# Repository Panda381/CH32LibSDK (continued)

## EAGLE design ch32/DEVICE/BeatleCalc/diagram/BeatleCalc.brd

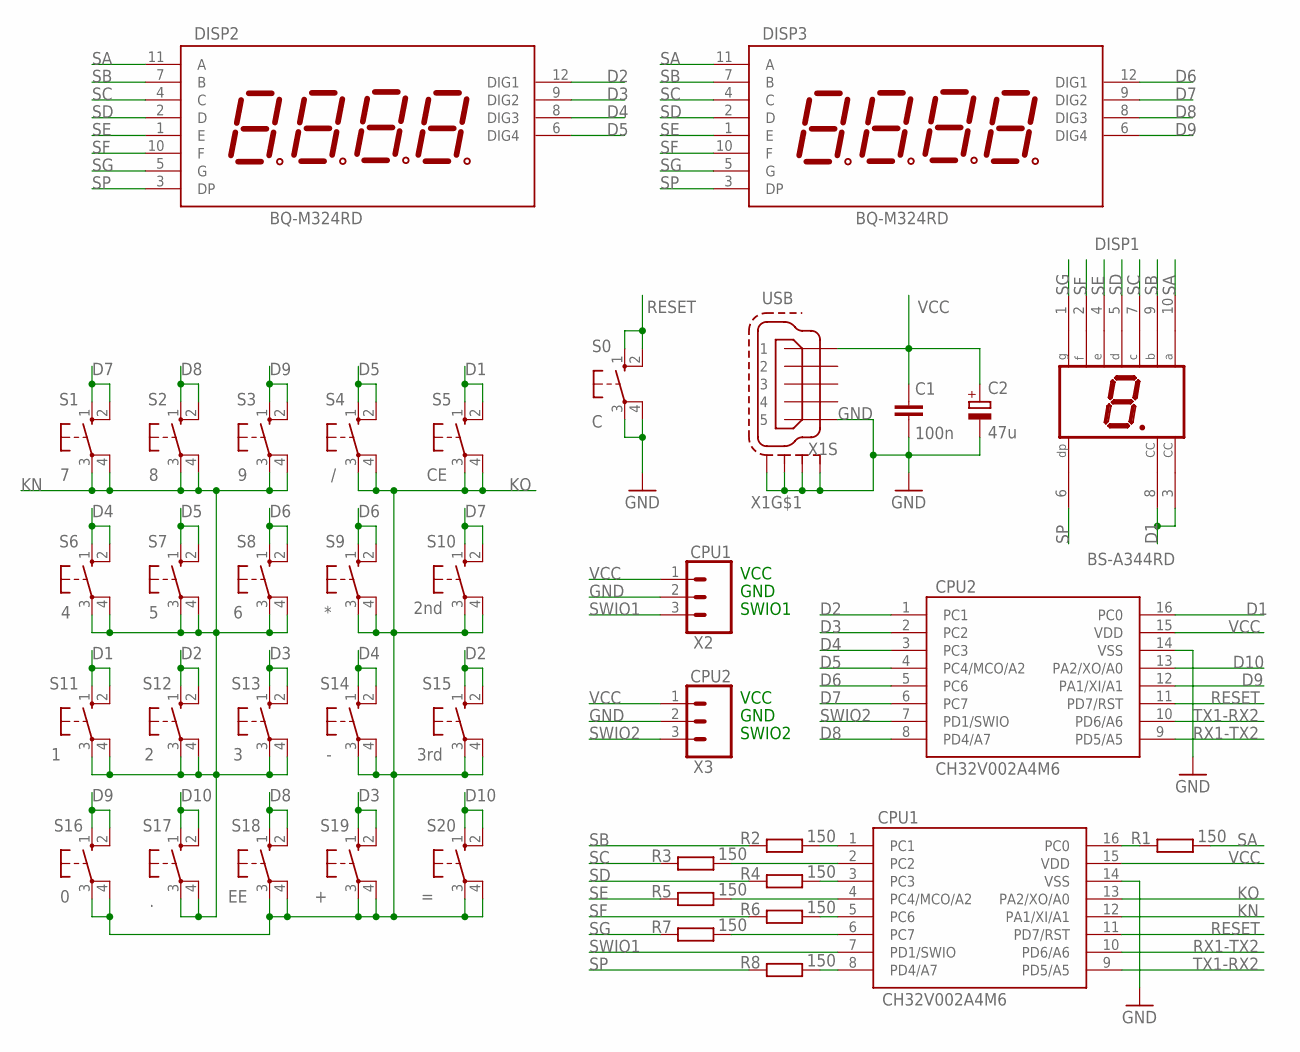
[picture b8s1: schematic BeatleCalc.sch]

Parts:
C1: 100n; C050-024X044
C2: 47u; TT2D6L
CPU1, CPU2: CH32V002A4M6; SOP16
DISP1: BS-A344RD; HDSP-E
DISP2, DISP3: BQ-M324RD; 4DIG_7SEG_92MM
R1, R2, R3, R4, R5, R6, R7, R8: 150; 0204/10
S0: C; B3F-10XX
S1: 7; B3F-10XX
S2: 8; B3F-10XX
S3: 9; B3F-10XX
S4: /; B3F-10XX
S5: CE; B3F-10XX
S6: 4; B3F-10XX
S7: 5; B3F-10XX
S8: 6; B3F-10XX
S9: *; B3F-10XX
S10: 2nd; B3F-10XX
S11: 1; B3F-10XX
S12: 2; B3F-10XX
S13: 3; B3F-10XX
S14: -; B3F-10XX
S15: 3rd; B3F-10XX
S16: 0; B3F-10XX
S17: .; B3F-10XX
S18: EE; B3F-10XX
S19: +; B3F-10XX
S20: =; B3F-10XX
X1: USB; 32005-201
X2: CPU1; 1X03_LONGPADS
X3: CPU2; 1X03_LONGPADS

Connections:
D1: CPU2.16 (PC0), DISP1.3 (CC), DISP1.8 (CC), S5.1 (S), S5.2 (S1), S11.1 (S), S11.2 (S1)
D2: CPU2.1 (PC1), DISP2.12 (DIG1), S12.1 (S), S12.2 (S1), S15.1 (S), S15.2 (S1)
D3: CPU2.2 (PC2), DISP2.9 (DIG2), S13.1 (S), S13.2 (S1), S19.1 (S), S19.2 (S1)
D4: CPU2.3 (PC3), DISP2.8 (DIG3), S6.1 (S), S6.2 (S1), S14.1 (S), S14.2 (S1)
D5: CPU2.4 (PC4/MCO/A2), DISP2.6 (DIG4), S4.1 (S), S4.2 (S1), S7.1 (S), S7.2 (S1)
D6: CPU2.5 (PC6), DISP3.12 (DIG1), S8.1 (S), S8.2 (S1), S9.1 (S), S9.2 (S1)
D7: CPU2.6 (PC7), DISP3.9 (DIG2), S1.1 (S), S1.2 (S1), S10.1 (S), S10.2 (S1)
D8: CPU2.8 (PD4/A7), DISP3.8 (DIG3), S2.1 (S), S2.2 (S1), S18.1 (S), S18.2 (S1)
D9: CPU2.12 (PA1/XI/A1), DISP3.6 (DIG4), S3.1 (S), S3.2 (S1), S16.1 (S), S16.2 (S1)
D10: CPU2.13 (PA2/XO/A0), S17.1 (S), S17.2 (S1), S20.1 (S), S20.2 (S1)
GND: C1.2, C2.-, CPU1.14 (VSS), CPU2.14 (VSS), S0.3, S0.4 (P1), X1.5, X1.M1 (S1), X1.M2 (S2), X1.M3 (S3), X1.M4 (S4), X2.2, X3.2
KN: CPU1.12 (PA1/XI/A1), S1.3, S1.4 (P1), S2.3, S2.4 (P1), S3.3, S3.4 (P1), S6.3, S6.4 (P1), S7.3, S7.4 (P1), S8.3, S8.4 (P1), S11.3, S11.4 (P1), S12.3, S12.4 (P1), S13.3, S13.4 (P1), S17.3, S17.4 (P1)
KO: CPU1.13 (PA2/XO/A0), S4.3, S4.4 (P1), S5.3, S5.4 (P1), S9.3, S9.4 (P1), S10.3, S10.4 (P1), S14.3, S14.4 (P1), S15.3, S15.4 (P1), S16.3, S16.4 (P1), S18.3, S18.4 (P1), S19.3, S19.4 (P1), S20.3, S20.4 (P1)
unnamed: CPU1.1 (PC1), R2.2
unnamed: CPU1.2 (PC2), R3.2
unnamed: CPU1.3 (PC3), R4.2
unnamed: CPU1.4 (PC4/MCO/A2), R5.2
unnamed: CPU1.5 (PC6), R6.2
unnamed: CPU1.6 (PC7), R7.2
unnamed: CPU1.8 (PD4/A7), R8.2
unnamed: CPU1.16 (PC0), R1.1
RESET: CPU1.11 (PD7/RST), CPU2.11 (PD7/RST), S0.1 (S), S0.2 (S1)
RX1-TX2: CPU1.10 (PD6/A6), CPU2.9 (PD5/A5)
SA: DISP1.10 (A), DISP2.11 (A), DISP3.11 (A), R1.2
SB: DISP1.9 (B), DISP2.7 (B), DISP3.7 (B), R2.1
SC: DISP1.7 (C), DISP2.4 (C), DISP3.4 (C), R3.1
SD: DISP1.5 (D), DISP2.2 (D), DISP3.2 (D), R4.1
SE: DISP1.4 (E), DISP2.1 (E), DISP3.1 (E), R5.1
SF: DISP1.2 (F), DISP2.10 (F), DISP3.10 (F), R6.1
SG: DISP1.1 (G), DISP2.5 (G), DISP3.5 (G), R7.1
SP: DISP1.6 (DP), DISP2.3 (DP), DISP3.3 (DP), R8.1
SWIO1: CPU1.7 (PD1/SWIO), X2.3
SWIO2: CPU2.7 (PD1/SWIO), X3.3
TX1-RX2: CPU1.9 (PD5/A5), CPU2.10 (PD6/A6)
VCC: C1.1, C2.+, CPU1.15 (VDD), CPU2.15 (VDD), X1.1, X2.1, X3.1

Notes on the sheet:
VCC
GND
SWIO2
SWIO1

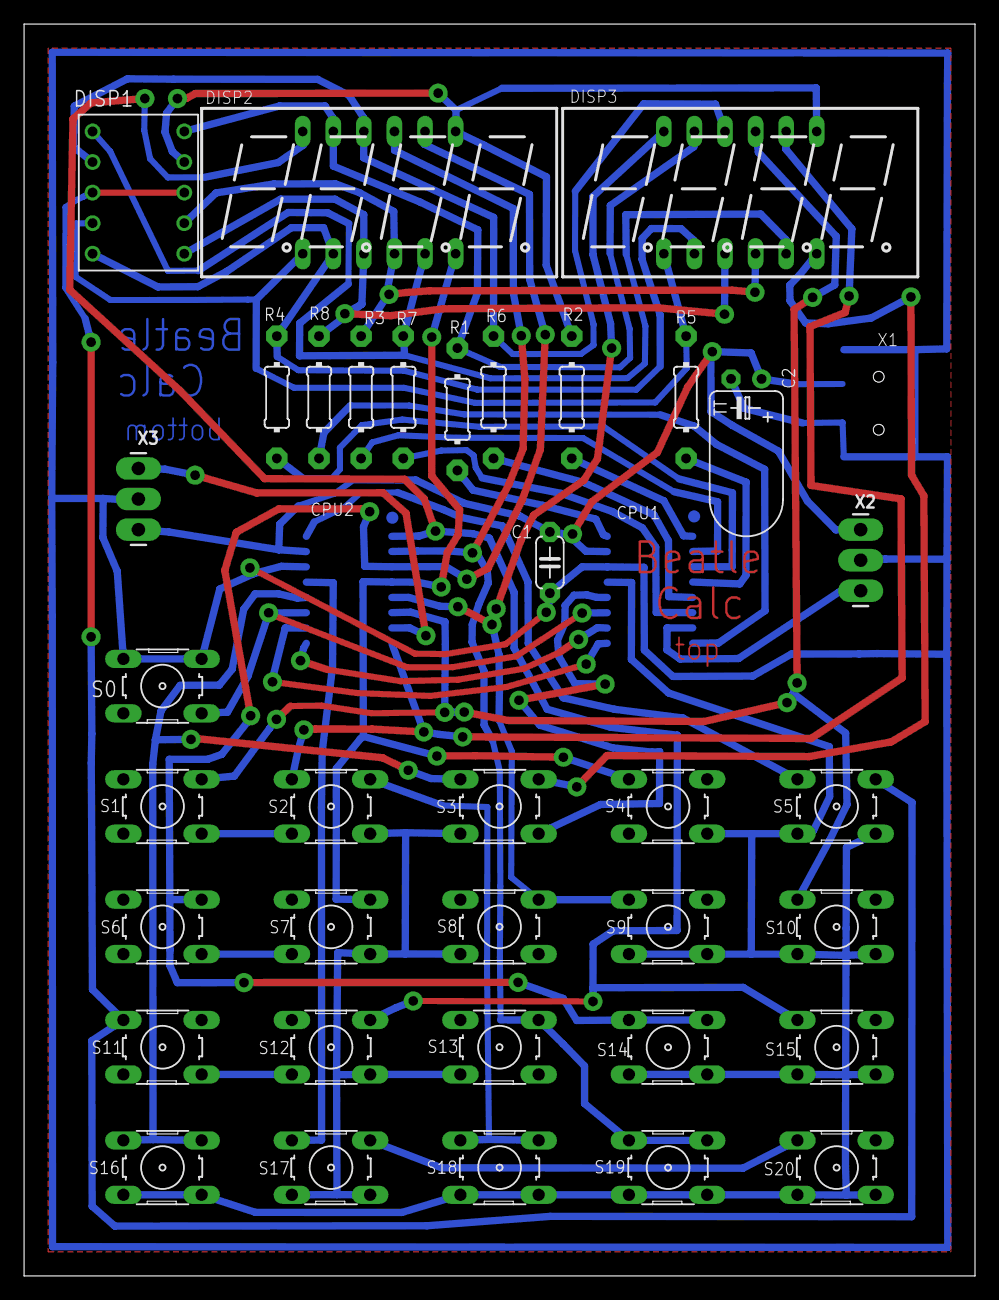
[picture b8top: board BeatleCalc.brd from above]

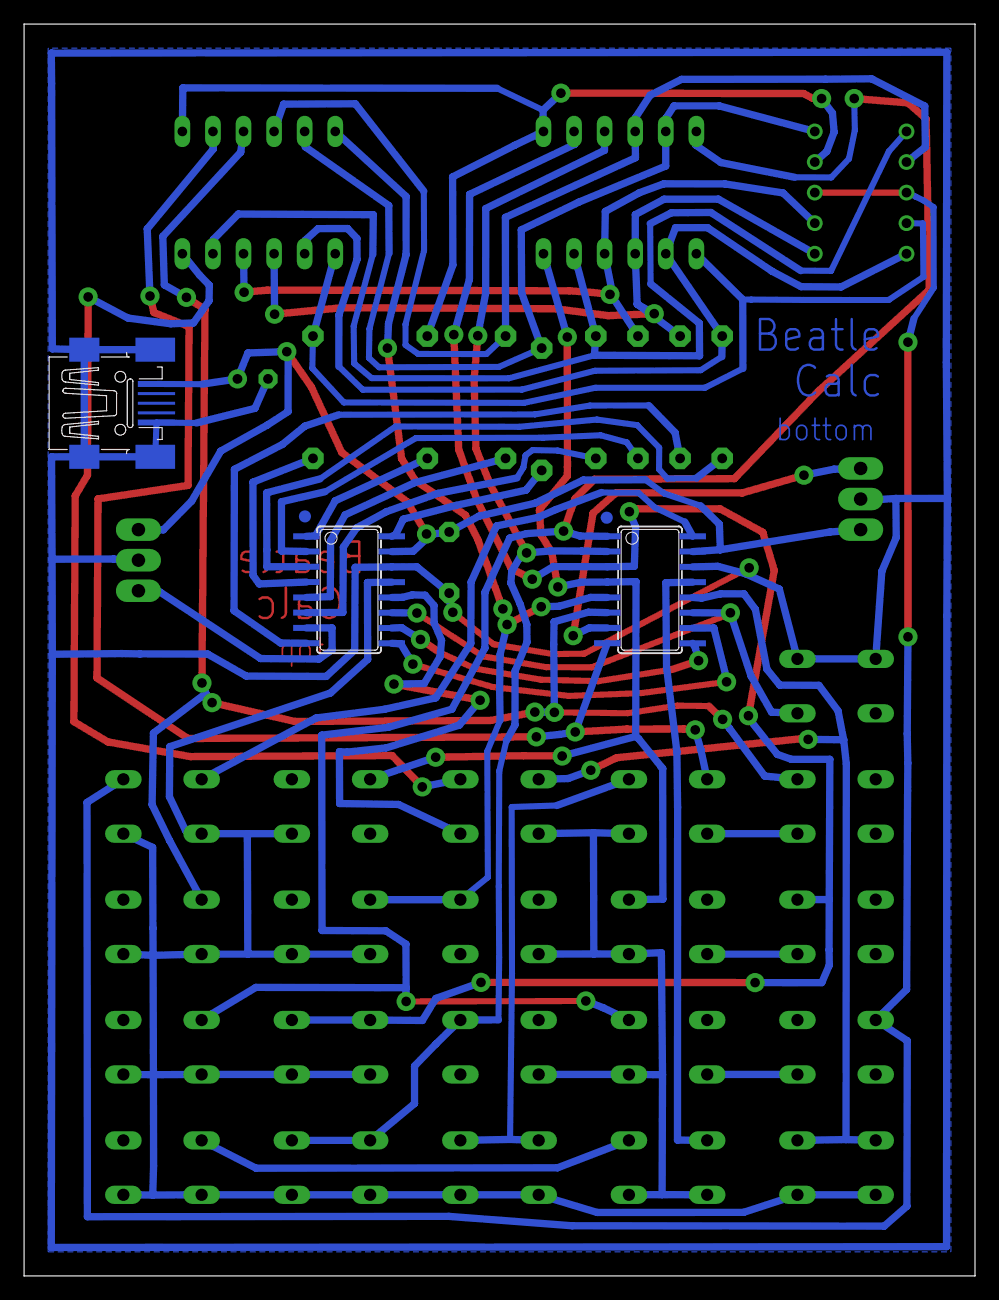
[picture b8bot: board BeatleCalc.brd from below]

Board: 2 copper layers, 79.0 x 104.0 mm, 39 parts (3 on the bottom side), 35 nets.

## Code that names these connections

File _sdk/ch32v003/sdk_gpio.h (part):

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INLINE void GPIOA_Out1(int pin) { GPIOx_Out1(GPIOA, pin); }
INLINE void GPIOC_Out1(int pin) { GPIOx_Out1(GPIOC, pin); }
INLINE void GPIOD_Out1(int pin) { GPIOx_Out1(GPIOD, pin); }
INLINE void GPIO_Out1(int gpio) { GPIOx_Out1(GPIO_PORT(gpio), GPIO_PIN(gpio)); }

// output value to GPIO output pin (val = 0 or <>0; port = GPIOA..., pin = 0.., gpio = PA0...)
//  In GPIO_MODE_IN_* modes 0 selects pull-down mode, <>0 selects pull-up mode.
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INLINE void GPIO_Remap1_3b(int pos, int map) { AFIO->PCFR1 = (AFIO->PCFR1 & ~(7 << pos)) | (map << pos); }

// Remap SPI1 (default 0)
//	0 ... PC1:CS, PC5:SCK, PC7:MISO, PC6:MOSI
//	1 ... PC0:CS, PC5:SCK, PC7:MISO, PC6:MOSI
INLINE void GPIO_Remap_SPI1(int map) { GPIO_Remap1_1b(0, map); }

// Remap I2C1 (default 0)
//	0 ... PC2:SCL, PC1:SDA
//	1 ... PD1:SCL, PD0:SDA
//	2,3 ... PC5:SCL, PC6:SDA
INLINE void GPIO_Remap_I2C1(int map) { AFIO->PCFR1 = (AFIO->PCFR1 & ~(B1|B22)) | ((map & B0) << 1) | ((map >> 1) << 22); }

// Remap USART1 (default 0)
//	0 ... PD5:TX, PD6:RX, PD4:CLK, PD3:CTS, PC2:RTS
//	1 ... PD0:TX, PD1:RX, PD7:CLK, PC3:CTS, PC2:RTS, PD0:SW_RX
//	2 ... PD6:TX, PD5:RX, PD7:CLK, PC6:CTS, PC7:RTS, PD6:SW_RX
//	3 ... PC0:TX, PC1:RX, PC5:CLK, PC6:CTS, PC7:RTS, PC0:SW_RX
INLINE void GPIO_Remap_USART1(int map) { AFIO->PCFR1 = (AFIO->PCFR1 & ~(B2|B21)) | ((map & B0) << 2) | ((map >> 1) << 21); }

// Remap Timer 1 (default 0)
//	0 ... PC5:ETR, PD2:CH1, PA1:CH2, PC3:CH3, PC4:CH4, PC2:BKIN, PD0:CH1N, PA2:CH2N, PD1:CH3N
//	1 ... PC5:ETR, PC6:CH1, PC7:CH2, PC0:CH3, PD3:CH4, PC1:BKIN, PC3:CH1N, PC4:CH2N, PD1:CH3N
//	2 ... PD4:ETR, PD2:CH1, PA1:CH2, PC3:CH3, PC4:CH4, PC2:BKIN, PD0:CH1N, PA2:CH2N, PD1:CH3N
//	3 ... PC2:ETR, PC4:CH1, PC7:CH2, PC5:CH3, PD4:CH4, PC1:BKIN, PC3:CH1N, PD2:CH2N, PC6:CH3N
INLINE void GPIO_Remap_TIM1(int map) { GPIO_Remap1_2b(6, map); }

// Remap Timer 2 (default 0)
//	0 ... PD4:CH1/ETR, PD3:CH2, PC0:CH3, PD7:CH4
//	1 ... PC5:CH1/ETR, PC2:CH2, PD2:CH3, PC1:CH4
//	2 ... PC1:CH1/ETR, PD3:CH2, PC0:CH3, PD7:CH4
//	3 ... PC1:CH1/ETR, PC7:CH2, PD6:CH3, PD5:CH4
INLINE void GPIO_Remap_TIM2(int map) { GPIO_Remap1_2b(8, map); }

// Remap PA1 & PA2 pins to OSC_IN & OSC_OUT (default 0)
//	0 ... pins PA1 & PA2 are used as GPIO ports
//	1 ... pins PA1 & PA2 are used as crystal pins OSC_IN & OSC_OUT
INLINE void GPIO_Remap_PA1PA2(int map) { GPIO_Remap1_1b(15, map); }

// Remap ADC1 external trigger injection conversion (default 0)
//	0 ... ADC1 external trigger injection conversion connected to PD3
//	1 ... ADC1 external trigger injection conversion connected to PC2
INLINE void GPIO_Remap_ADC1INJ(int map) { GPIO_Remap1_1b(17, map); }

// Remap ADC1 external trigger regular conversion (default 0)
//	0 ... ADC1 external trigger regular conversion connected to PD3
//	1 ... ADC1 external trigger regular conversion connected to PC2
INLINE void GPIO_Remap_ADC1REG(int map) { GPIO_Remap1_1b(18, map); }

// Remap Timer 1 Channel 1 (default 0)
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
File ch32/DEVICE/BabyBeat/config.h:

// ****************************************************************************
//                                 
//                        Project library configuration
//
// ****************************************************************************

#ifndef _CONFIG_H
#define _CONFIG_H

// Pre-set defines (use #if to check):
//	target MCU	MCU serie	MCU class	MCU subclass
//	CH32V002x4	CH32V002	CH32V0		CH32V00X
//	CH32V003x4	CH32V003	CH32V0
//	CH32V004x6	CH32V004	CH32V0		CH32V00X
//	CH32V005x6	CH32V005	CH32V0		CH32V00X
//	CH32V006x4	CH32V006	CH32V0		CH32V00X
//	CH32V006x8	CH32V006	CH32V0		CH32V00X
//	CH32V007x8	CH32V007	CH32V0		CH32V00X
//	CH32X033x8	CH32V033	CH32V0		CH32V03X
//	CH32X035x7	CH32V035	CH32V0		CH32V03X
//	CH32X035x8	CH32V035	CH32V0		CH32V03X
//	CH32V103x6	CH32V103	CH32V1
//	CH32V103x8	CH32V103	CH32V1
//	CH32L103x8	CH32L103	CH32V1

// FLASHSIZE ... Flash size in bytes
// RAMSIZE ... RAM size in bytes
// STACKSIZE ... Stack size in bytes

#define BABYBEAT	1	// 1 = use BabyBeat device
//#define BEATLEBEAT	1	// 1 = use BeatleBeat device

#if BABYBEAT		// 1 = use BabyBeat device
#define SYSTICK_KEYSCAN	1	// 1=call KeyScan() function from SysTick system timer
#else
#define SYSTICK_KEYSCAN	0	// 1=call KeyScan() function from SysTick system timer
#endif

// ----------------------------------------------------------------------------
//                            Clock Setup
// ----------------------------------------------------------------------------

// frequency of HSI internal oscillator 48MHz
#define HSI_VALUE	24000000

// System clock source: 1=HSI, 2=HSE, 3=HSE_Bypass, 4=PLL_HSI, 5=PLL_HSE, 6=PLL_HSE_Bypass, 7=PLL_HSI/2, 8=PLL_HSE/2, 9=PLL_HSE_Bypass/2
#define SYSCLK_SRC	4

// PLL multiplier
#define PLLCLK_MUL	2		// only *2 supported; 24 MHz * 2 = 48 MHz

// System clock divider: 1, 2, 3, 4, 5, 6, 7, 8, 16, 32, 64, 128, 256 (default 1)
#define SYSCLK_DIV	1

// ADC clock divider: (1,) 2, 4, 6, 8, 12, 16, 24, 32, 48, 64, 96, 128 (default 1 or 2)
#define ADCCLK_DIV	8		// CH32V0: max. 24 MHz (48 / 8 = 6 MHz)

// number of HCLK clock cycles per 1 us (used with Wait functions)
// - If you want to change frequency of system clock run-time, use a variable instead of constant.
#define HCLK_PER_US	48

// increment of system time in [ms] on SysTick interrupt (0=do not use SysTick interrupt)
#if BABYBEAT		// 1 = use BabyBeat device
#define SYSTICK_MS	20
#else
#define SYSTICK_MS	0
#endif

// ----------------------------------------------------------------------------
//                          Peripheral clock enable
// ----------------------------------------------------------------------------

#define ENABLE_SRAM	1		// SRAM enable
#define ENABLE_FLASH	0		// FLASH enable
#define ENABLE_WWDG	0		// Window watchdog enable
#define ENABLE_PWR	1		// Power module enable
#define ENABLE_AFI	1		// I/O auxiliary function enable
#define ENABLE_PA	1		// PA port enable
#define ENABLE_PB	0		// PB port enable
#define ENABLE_PC	1		// PC port enable
#define ENABLE_PD	1		// PD port enable
#define ENABLE_ADC1	0		// ADC1 module enable
#define ENABLE_TIM1	1		// TIM1 module enable
#define ENABLE_TIM2	0		// TIM2 module enable
#define ENABLE_TIM3	0		// TIM3 module enable
#define ENABLE_SPI1	0		// SPI1 module enable
#define ENABLE_USART1	0		// USART1 module enable
#define ENABLE_I2C1	0		// I2C1 module enable
#define ENABLE_DMA1	0		// DMA1 module enable

// ----------------------------------------------------------------------------
//                            Library modules
// ----------------------------------------------------------------------------

#define USE_CRC		0	// 1=use CRC library
#define USE_DECNUM	0	// 1=use decode number
#define USE_FAT		1	// 1=use FAT filesystem
#define USE_RAND	0	// 1=use random number generator

// SD card
#if BABYBEAT		// 1 = use BabyBeat device
// Note: cannot use hardware SPI at this CPU, mappings 3 and 4 are not working.
#define SD_CS_GPIO	PA1	// CS output to SD card
#define SD_CLK_GPIO	PD4	// CLK output to SD card
#define SD_MISO_GPIO	PD5	// MISO input from SD card
#define SD_MOSI_GPIO	PD6	// MOSI output to SD card
#else // BABYBEAT
// SD card
#define SD_CS_GPIO	PC4	// CS output to SD card
#define SD_CLK_GPIO	PC2	// CLK output to SD card
#define SD_MISO_GPIO	PC1	// MISO input from SD card
#define SD_MOSI_GPIO	PD1	// MOSI output to SD card
#endif // BABYBEAT
#define USE_SD		3	// use SD card driver: 0=no, 1=software, 2=hardware (with software CS), 3=software with fast read
#define SD_SPEED_INIT	(HCLK_PER_US*2)	// SD speed on init: wait delay "HCLK_PER_US*2" = 250 kbps
#define SD_SPEED_READ	3	// (working value 0..3) SD speed on read: wait delay "HCLK_PER_US/8" = 4 Mbps
#define SD_SPEED_WRITE	(HCLK_PER_US/2)	// SD speed on write: wait delay "HCLK_PER_US/2" = 1 Mbps

// ----------------------------------------------------------------------------
//                             SDK modules
// ----------------------------------------------------------------------------

#define USE_ADC		0	// 1=use ADC peripheral
#define USE_DMA		0	// 1=use DMA peripheral
#define USE_FLASH	0	// 1=use Flash programming
#define USE_I2C		0	// 1=use I2C peripheral
#define USE_IRQ		1	// 1=use IRQ interrupt support
#define USE_PWR		1	// 1=use power control
#define USE_SPI		0	// 1=use SPI peripheral
#define USE_TIM		1	// 1=use timers
#define USE_USART	0	// 1=use USART peripheral

#endif // _CONFIG_H

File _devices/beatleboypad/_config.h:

// ----------------------------------------------------------------------------
//                            Clock Setup
// ----------------------------------------------------------------------------

// Frequency of HSE external oscillator
#ifndef HSE_VALUE
#define HSE_VALUE	24000000
#endif

// frequency of HSI internal oscillator
#ifndef HSI_VALUE
#define HSI_VALUE	24000000
#endif

// System clock source: 1=HSI, 2=HSE, 3=HSE_Bypass, 4=PLL_HSI, 5=PLL_HSE, 6=PLL_HSE_Bypass, 7=PLL_HSI/2, 8=PLL_HSE/2, 9=PLL_HSE_Bypass/2
#ifndef SYSCLK_SRC
#define SYSCLK_SRC	1
#endif

// PLL multiplier
#ifndef PLLCLK_MUL
#define PLLCLK_MUL	0		// only *2 supported; 24 MHz * 2 = 48 MHz
#endif

// System clock divider: 1, 2, 3, 4, 5, 6, 7, 8, 16, 32, 64, 128, 256 (default 1)
#ifndef SYSCLK_DIV
#define SYSCLK_DIV	1
#endif

// number of HCLK clock cycles per 1 us (used with Wait functions)
// - If you want to change frequency of system clock run-time, use a variable instead of constant.
#ifndef HCLK_PER_US
#define HCLK_PER_US	24
#endif

// ADC clock divider: (1,) 2, 4, 6, 8, 12, 16, 24, 32, 48, 64, 96, 128 (default 1 or 2)
#ifndef ADCCLK_DIV
#define ADCCLK_DIV	24		// CH32V0: max. 24 MHz (24 / 24 = 1 MHz)
#endif

// increment of system time in [ms] on SysTick interrupt (0=do not use SysTick interrupt)
#ifndef SYSTICK_MS
#define SYSTICK_MS	0
#endif

// ----------------------------------------------------------------------------
//                             Device setup
// ----------------------------------------------------------------------------

// run mode
#define RUNMODE_OLED	0	// hardcoded in beatleboypad_asm.S
#define RUNMODE_VGA	1

#ifndef DISP_DBLBUF
#define DISP_DBLBUF	0	// 1=use VGA display double buffer (FrameBuf+DispBuf)
#endif

// ADC measure
// - Buttons are valid if they are detected twice identically - so the reaction time is 2*32=64 ms.
#define PADADC_SHIFT	9	// bits of number of measures of PAD (= period 31.8us * 2 * 512 = 32ms)
#define PADADC_NUM	(1<<PADADC_SHIFT) // number of measures of PAD
#define SUPPLYADC_SHIFT	5	// bits of number of measures of supply voltage (= period 32ms * 32 = 1sec)
#define SUPPLYADC_NUM	(1<<SUPPLYADC_SHIFT) // number of measures of supply voltage

// Button codes (order corresponds to the order of the arrow characters in the font)
#define KEY_RIGHT	1	// right (character code 0x0C = arrow right, or ASCII code 0x1C)
#define KEY_UP		2	// up (character code 0x0D = arrow up, or ASCII code 0x1D)
#define KEY_LEFT	3	// left (character code 0x0E = arrow left, or ASCII code 0x1E)
#define KEY_DOWN	4	// down (character code 0x0F = arrow down, or ASCII code 0x1F)
#define KEY_A		5	// A
#define KEY_B		6	// B

#define NOKEY		0	// no key

#define KEY_NUM		6	// number of buttons

// display
#define DISP_I2C_ADDR	0x3C	// display I2C address
#define DISP_SDA_GPIO	PC1	// display gpio with SDA
#define DISP_SCL_GPIO	PC2	// display gpio with SCL
#define DISP_I2C_MAP	0	// hardware display driver: I2C mapping

#ifndef DISP_WAIT_CLK
#define DISP_WAIT_CLK	3	// software display driver: number of I2C wait clock (0 or more) ... DispUpdate() takes 2:10ms, 3-4:11ms, 10:26 ms
#endif

#ifndef DISP_SPEED_HZ
#define DISP_SPEED_HZ	750000	// hardware display driver: I2C speed in Hz ... DispUpdate() takes 3M:4ms, 2M:6ms, 1M:11ms, 500K:20ms
#endif

#ifndef USE_DISP
#define USE_DISP	1	// 1=use software I2C display driver, 2=use hardware I2C display driver, 0=no display driver
#endif

#ifndef USE_SD
#define USE_SD		0	// 1=use software SD card driver, 2=use hardware SD card driver (0=no driver)
#endif

#ifndef USE_DRAW
#define USE_DRAW	1	// 1=use graphics drawing functions
#endif

#ifndef USE_PRINT
#define USE_PRINT	1	// 1=use text printing functions
#endif

#ifndef USE_KEY
#define USE_KEY		1	// 1=use keyboard support
#endif

#ifndef USE_SOUND
#define USE_SOUND	2	// use sound support 1=tone, 2=melody
#endif

//#ifndef KEYCNT_REL
//#define KEYCNT_REL	4	// keyboard counter - release interval in 1/60 sec
//#endif

//#ifndef KEYCNT_PRESS
//#define KEYCNT_PRESS	20	// keyboard counter - first repeat in 1/60 sec
//#endif

//#ifndef KEYCNT_REPEAT
//#define KEYCNT_REPEAT	6	// keyboard counter - next repeat in 1/60 sec
//#endif

// do not use SysTick
//#define SYSTICK_KEYSCAN	0	// 1=call KeyScan() function from SysTick system timer
//#define SYSTICK_SOUNDSCAN 0	// 1=call SoundScan() function from SysTick system timer

// ----------------------------------------------------------------------------
//                          Peripheral clock enable
// ----------------------------------------------------------------------------

// Periferals
#ifndef ENABLE_SRAM
#define ENABLE_SRAM	1		// SRAM enable
#endif

#ifndef ENABLE_FLASH
#define ENABLE_FLASH	1		// FLASH enable (needed to rewrite RESET function)
#endif

#ifndef ENABLE_WWDG
#define ENABLE_WWDG	0		// Window watchdog enable
#endif

#ifndef ENABLE_PWR
#define ENABLE_PWR	1		// Power module enable
#endif

#ifndef ENABLE_AFI
#define ENABLE_AFI	1		// I/O auxiliary function enable
#endif

#ifndef ENABLE_PA
#define ENABLE_PA	1		// PA port enable
#endif

#ifndef ENABLE_PB
#define ENABLE_PB	1		// PB port enable
#endif

#ifndef ENABLE_PC
#define ENABLE_PC	1		// PC port enable
#endif

#ifndef ENABLE_PD
#define ENABLE_PD	1		// PD port enable
#endif

#ifndef ENABLE_ADC1
#define ENABLE_ADC1	1		// ADC1 module enable
#endif

#ifndef ENABLE_TIM1
#define ENABLE_TIM1	1		// TIM1 module enable
#endif

#ifndef ENABLE_TIM2
#define ENABLE_TIM2	1		// TIM2 module enable
#endif

#ifndef ENABLE_TIM3
#define ENABLE_TIM3	0		// TIM3 module enable
#endif

#ifndef ENABLE_SPI1
#define ENABLE_SPI1	0		// SPI1 module enable
#endif

#ifndef ENABLE_USART1
#define ENABLE_USART1	0		// USART1 module enable
#endif

#ifndef ENABLE_USART2
#define ENABLE_USART2	0		// USART2 module enable
#endif

#ifndef ENABLE_USART3
#define ENABLE_USART3	0		// USART3 module enable
#endif

#ifndef ENABLE_USART4
#define ENABLE_USART4	0		// USART4 module enable
#endif

#ifndef ENABLE_I2C1
#define ENABLE_I2C1	1		// I2C1 module enable
#endif

// ----------------------------------------------------------------------------
//                            Library modules
// ----------------------------------------------------------------------------

#ifndef USE_CRC
#define USE_CRC		0	// 1=use CRC library
#endif

#ifndef USE_DECNUM
#define USE_DECNUM	1	// 1=use decode number
#endif

#ifndef USE_FAT
#define USE_FAT		0	// 1=use FAT filesystem
#endif

#ifndef USE_RAND
#define USE_RAND	1	// 1=use random number generator
#endif

// ----------------------------------------------------------------------------
//                             SDK modules
// ----------------------------------------------------------------------------

#ifndef USE_ADC
#define USE_ADC		1	// 1=use ADC peripheral
#endif

#ifndef USE_DMA
#define USE_DMA		0	// 1=use DMA peripheral
#endif

#ifndef USE_FLASH
#define USE_FLASH	1	// 1=use Flash programming
#endif

#ifndef USE_I2C
#define USE_I2C		1	// 1=use I2C peripheral
#endif

#ifndef USE_IRQ
#define USE_IRQ		1	// 1=use IRQ interrupt support
#endif

#ifndef USE_PWR
#define USE_PWR		1	// 1=use power control
#endif

#ifndef USE_SPI
#define USE_SPI		1	// 1=use SPI peripheral
#endif

#ifndef USE_TIM
#define USE_TIM		1	// 1=use timers
#endif

#ifndef USE_USART
#define USE_USART	0	// 1=use USART peripheral
#endif

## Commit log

2025-10-28 init
